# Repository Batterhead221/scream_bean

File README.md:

# SCREAM_BEAN_REV_B

Project Status

This revision is intended to improve the original SCREAM_BEAN layout and move the board closer to a clean, buildable pedal PCB.

System Role

Guitar input
    ↓
input buffer / gain and clipping stages
    ↓
tone / level shaping
    ↓
output to amplifier or next pedal

Key Specs

Board role - Analog guitar drive/distortion pedal PCB
Revision - Rev B
Circuit style - Tube Screamer-inspired overdrive/distortion
Sound target - Early-2000s pop-punk drive
Power direction - 9V pedal supply / battery-style pedal ecosystem
Controls - Drive / tone / level style pedal controls
Audio path - Analog
Board type - Stompbox effects pedal PCB

Main Features

Analog guitar input/output signal path
Drive/clipping stage
Tone-shaping network
Output level control
Pedal-style power input direction
Compact board layout for enclosure use
Silkscreen labels for bring-up and assembly
Revision B layout improvements

SCREAM_BEAN_REV_B is inspired by the Tube Screamer topology, but it is not meant to be a component-perfect clone.

Design priorities:

Build a working analog drive circuit
Learn op-amp gain/clipping behavior
Shape the tone for pop-punk rhythm guitar
Keep the board understandable and buildable
Use layout practices that make audio debugging easier

Power Notes

Pedal power should be treated carefully.

pedal supply / battery input
        ↓
protection / filtering
        ↓
audio circuit power rail

Common first checks:
no sound      → check power, input/output jack wiring, IC orientation
weak sound    → check gain stage values and pot wiring
harsh/fizzy   → check clipping diode orientation and tone network
hum/noise     → check grounding and cable/enclosure wiring
oscillation   → check layout, power decoupling, and high-gain routing

Design Notes
Keep audio input routing away from noisy power routing.
Keep gain-stage feedback paths short.
Keep power decoupling close to the IC.
Use clear labels for pots, jacks, power, and switch wiring.
Confirm enclosure fit before ordering a panelized or final version.
Expect component value experiments while tuning the sound.

Repository Output Images

Expected image paths for GitHub README rendering:

Outputs/
  IMG/
    3D-T.png
    3D-B.png
    SCHEMATIC.png
    L1-SIG.png
    L2-GND.png

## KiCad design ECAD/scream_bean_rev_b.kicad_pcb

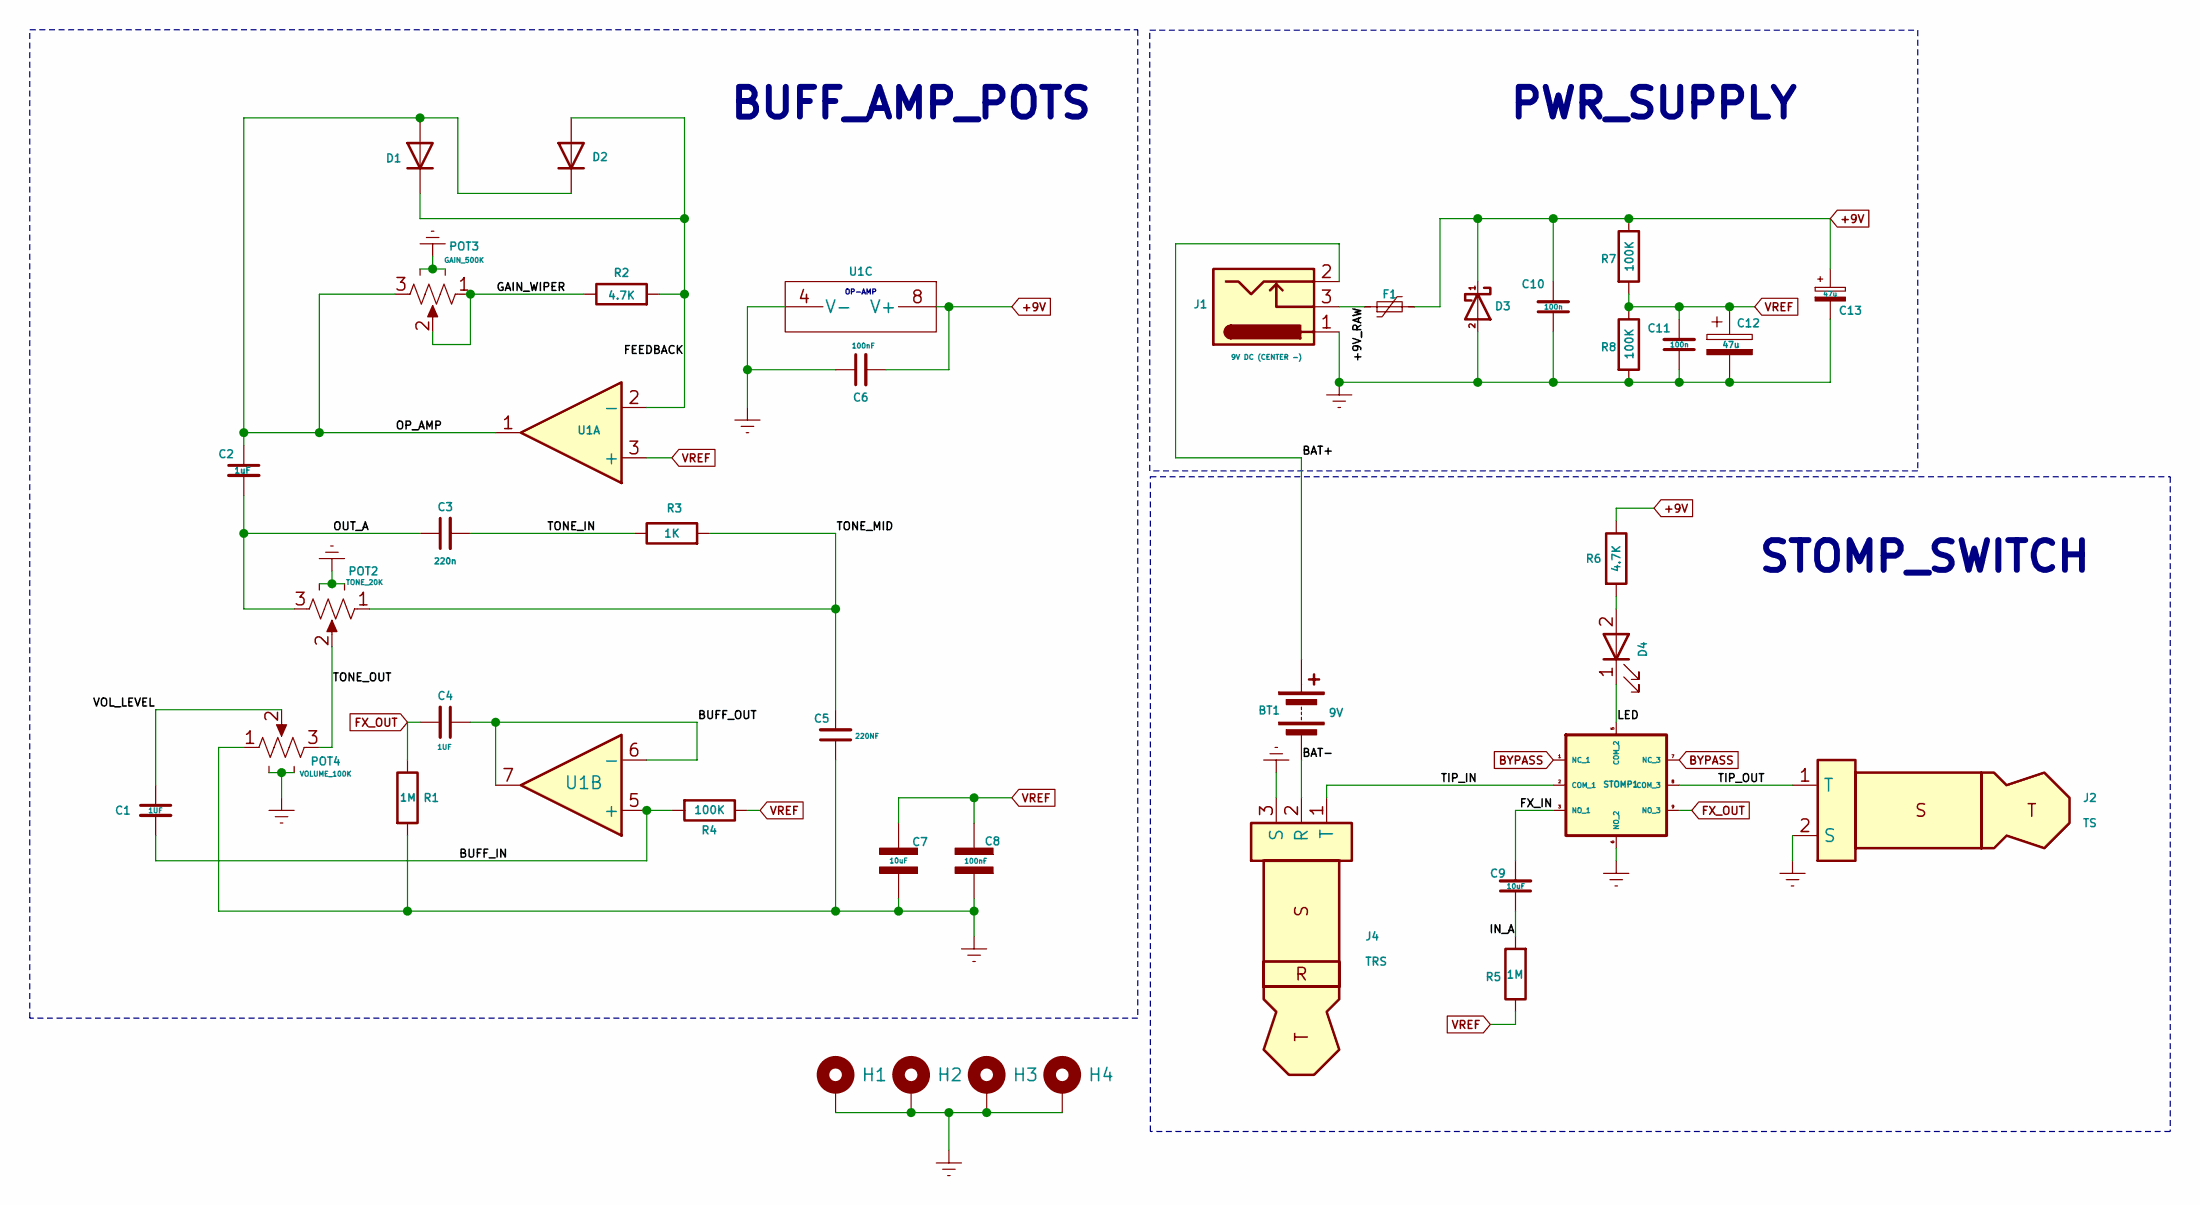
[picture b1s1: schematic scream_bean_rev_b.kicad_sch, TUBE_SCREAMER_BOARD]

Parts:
BT1: 9V; PinHeader_1x02_P2.54mm_Vertical
C1, C4: 1UF; C_0805_2012Metric; Voltage 25V; Tolerance 20%
C2: 1uF; C_0805_2012Metric; Voltage 6.3V; Tolerance 20%
C3: 220n; C_0603_1608Metric; Voltage 25V; Tolerance 20%
C5: 220NF; C_0603_1608Metric; Voltage 6.3V; Tolerance 20%
C6: 100nF; C_0805_2012Metric; Voltage 25V; Tolerance 20%
C7: 10uF; C_1206_3216Metric; DigiKey_Part_Number 490-18214-1-ND
C8: 100nF; C_0805_2012Metric; DigiKey_Part_Number 490-3261-1-ND
C9: 10uF; C_1206_3216Metric; Voltage 25V; Tolerance 20%
C10, C11: 100n; C_0805_2012Metric; Voltage 6.3V; Tolerance 20%
C12: 47u; CAP_EEEFK1E470P
C13: 47u; CAP_EEEFK1E470P; Voltage 6.3V; Tolerance 20%
D1, D2: 1N4148; D_SMA
D3: 1N5817; D_SMA
D4: LED; PinHeader_1x02_P2.54mm_Vertical
F1: Polyfuse_Small; Fuse_1210_3225Metric
H1, H2, H3, H4: MountingHole; MountingHole_3.2mm_M3_ISO14580_Pad_TopBottom
J1: 9V DC (CENTER -); BarrelJack_GCT_DCJ200-10-A_Horizontal
J2: TS; Jack_6.35mm_Neutrik_NMJ4HCD2_Horizontal
J4: TRS; Jack_6.35mm_Neutrik_NMJ6HCD2_Horizontal
POT2: TONE_20K; RD901F4015R1B100K00DL1
POT3: GAIN_500K; RD901F4015R1B100K00DL1
POT4: VOLUME_100K; RD901F4015R1B100K00DL1
R1, R5: 1M; R_0603_1608Metric
R2, R6: 4.7K; R_0603_1608Metric
R3: 1K; R_0603_1608Metric
R4, R7, R8: 100K; R_0603_1608Metric
STOMP1: FS57003PLT2B2M2QE; SW_FS57003PLT2B2M2QE
U1: NJM4558; SOIC127P680X200-8N

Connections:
+9V: C6.2, C10.2, C13.1, D3.1 (K), F1.2, R6.1, R7.1, U1.8 (V+)
/+9V_RAW: F1.1, J1.3 (GNDBREAK)
/BAT+: BT1.1 (+), J1.2 (GND)
/BAT-: BT1.2 (-), J4.2 (R)
/BUFF_IN: C1.2, R4.2, U1.5 (+)
/BUFF_OUT: C4.1, U1.6 (-), U1.7
/FEEDBACK: D1.1 (K), D2.2 (A), R2.2, U1.2 (-)
/FX_IN: C9.2, STOMP1.3 (NO_1)
/GAIN_WIPER: POT3.1, POT3.2, R2.1
/IN_A: C9.1, R5.2
/LED: D4.1 (K), STOMP1.5 (COM_2)
/OP_AMP: C2.1, D1.2 (A), D2.1 (K), POT3.3, U1.1
/OUT_A: C2.2, C3.1, POT2.3
/TIP_IN: J4.1 (T), STOMP1.2 (COM_1)
/TIP_OUT: J2.1 (T), STOMP1.8 (COM_3)
/TONE_IN: C3.2, R3.1
/TONE_MID: C5.2, POT2.1, R3.2
/TONE_OUT: POT2.2, POT4.3
/VOL_LEVEL: C1.1, POT4.2
BYPASS: STOMP1.1 (NC_1), STOMP1.7 (NC_3)
EARTH: C5.1, C6.1, C7.1, C8.1, C10.1, C11.1, C12.2, C13.2, D3.2 (A), H1.1 (1_1), H2.1 (1_1), H3.1 (1_1), H4.1 (1_1), J1.1 (PWR), J2.2 (S), J4.3 (S), POT2.4 (CASE), POT2.5 (CASE), POT3.4 (CASE), POT3.5 (CASE), POT4.1, POT4.4 (CASE), POT4.5 (CASE), R1.2, R8.2, STOMP1.6 (NO_2), U1.4 (V-)
FX_OUT: C4.2, R1.1, STOMP1.9 (NO_3)
unnamed: D4.2 (A), R6.2
VREF: C7.2, C8.2, C11.2, C12.1, R4.1, R5.1, R7.2, R8.1, U1.3 (+)

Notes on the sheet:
OP-AMP
STOMP_SWITCH
PWR_SUPPLY
BUFF_AMP_POTS

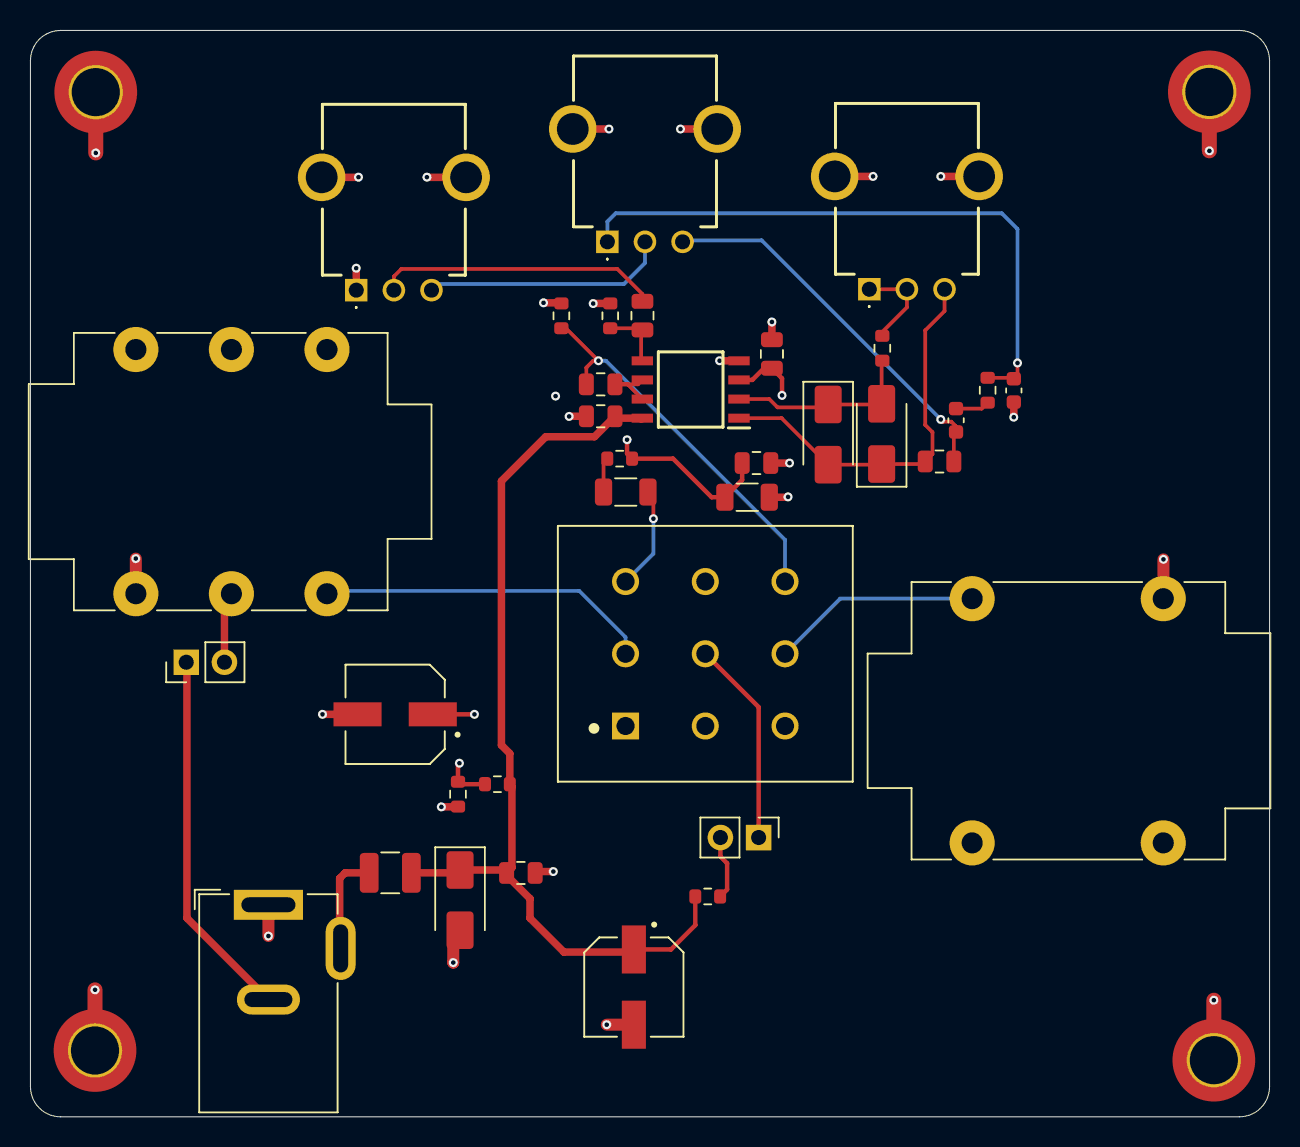
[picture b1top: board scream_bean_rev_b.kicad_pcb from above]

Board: 4 copper layers, 82.3 x 72.2 mm, 39 parts (0 on the bottom side), 24 nets.

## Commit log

2026-05-24 readme
